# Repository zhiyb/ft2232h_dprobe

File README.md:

# ft2232h_dprobe
FT2232H debug probe

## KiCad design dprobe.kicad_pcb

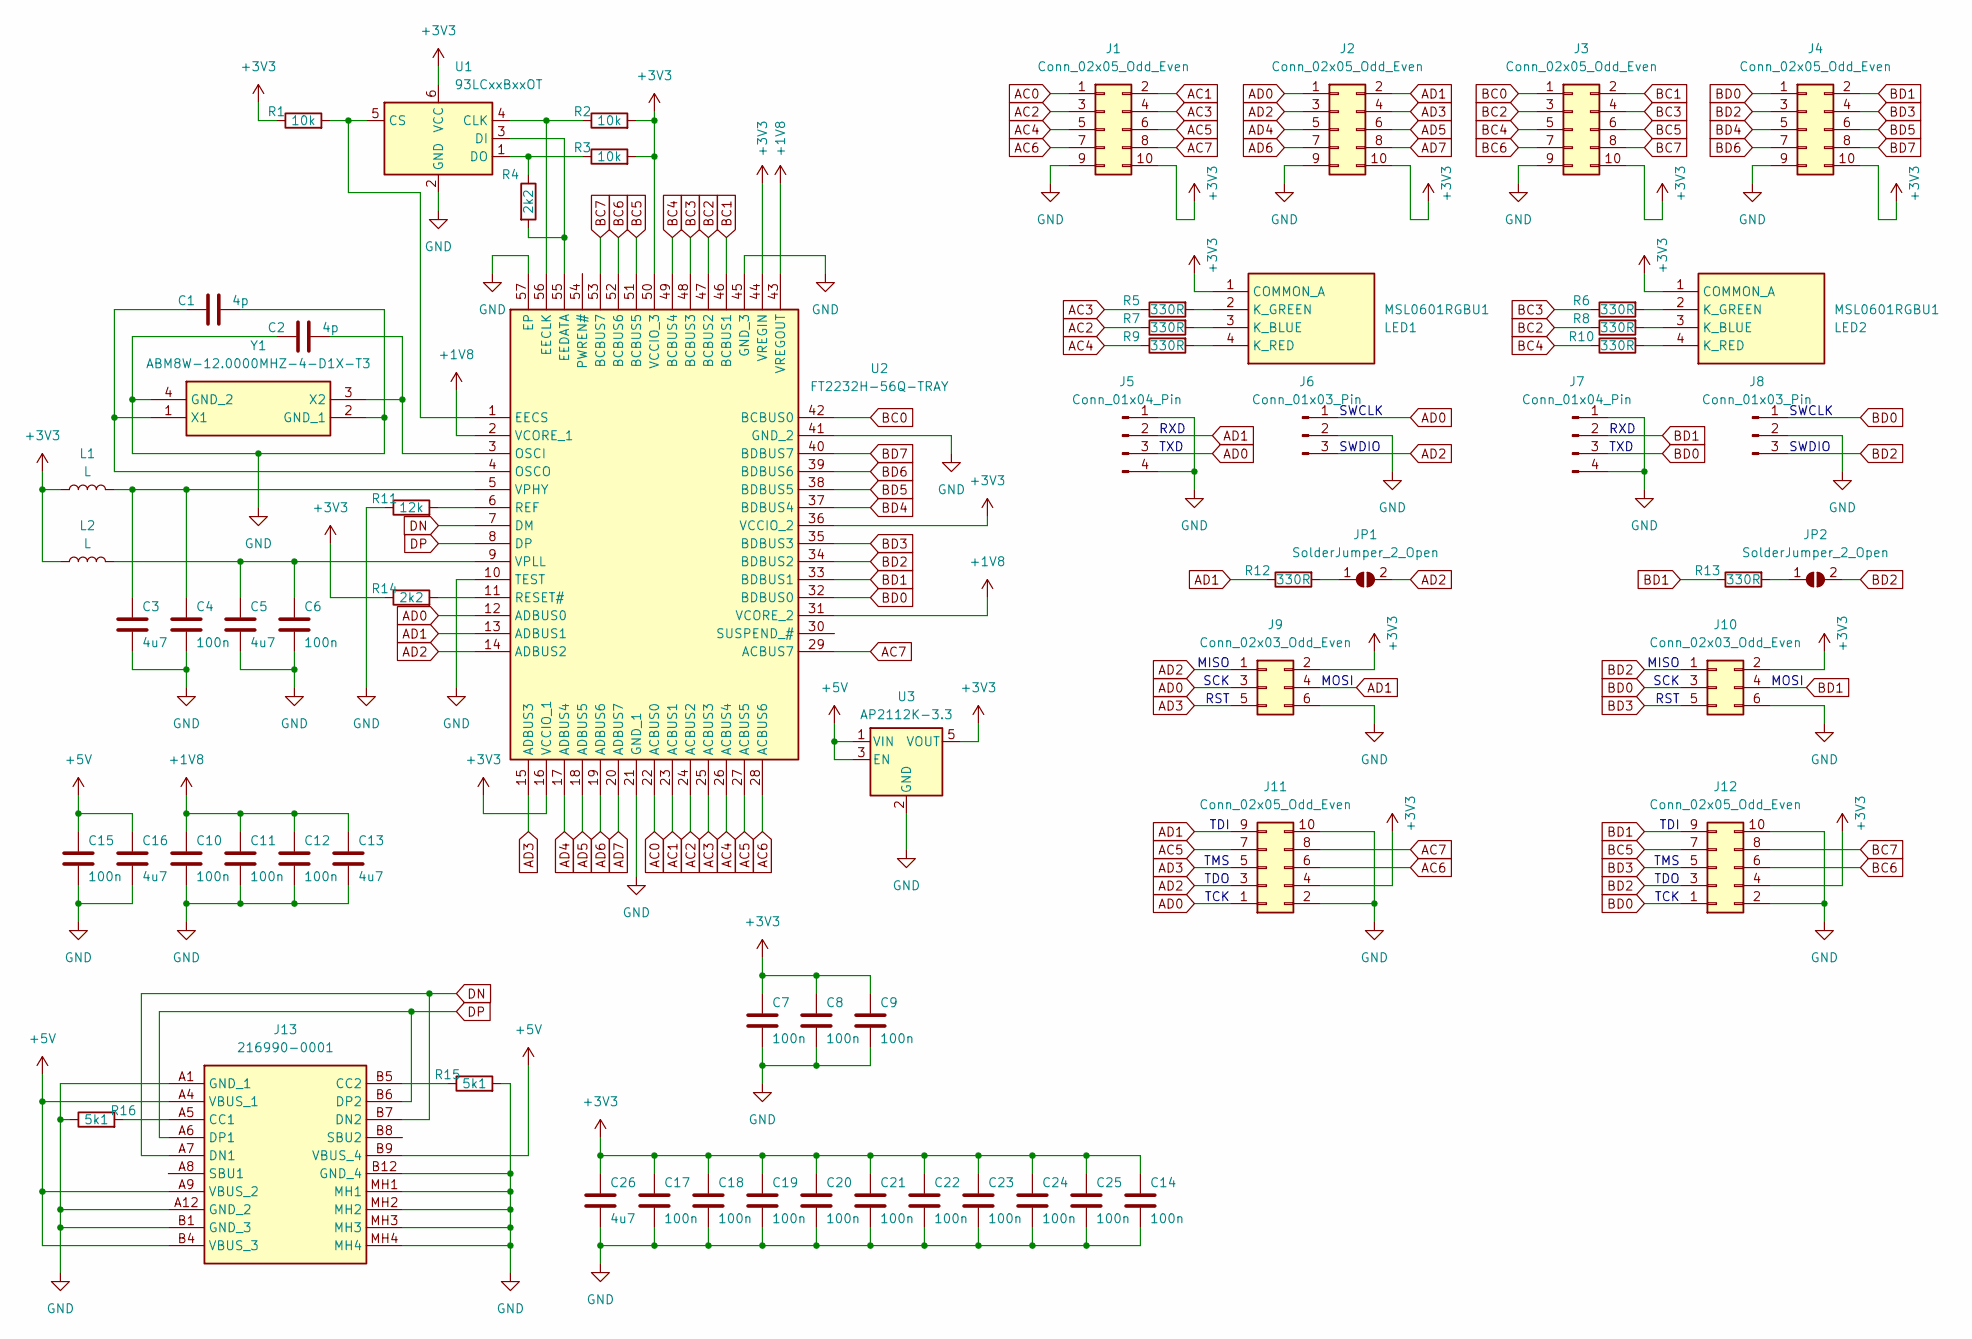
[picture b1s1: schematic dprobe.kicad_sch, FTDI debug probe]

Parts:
C1, C2: 4p; C_0402_1005Metric_Pad0.74x0.62mm_HandSolder
C3, C5, C13, C16, C26: 4u7; C_0402_1005Metric_Pad0.74x0.62mm_HandSolder
C4, C6, C7, C8, C9, C10, C11, C12, C14, C15, C17, C18, C19, C20, C21, C22, C23, C24, C25: 100n; C_0402_1005Metric_Pad0.74x0.62mm_HandSolder
J1, J2, J3, J4, J11, J12: Conn_02x05_Odd_Even; PinHeader_2x05_P2.54mm_Vertical
J5, J7: Conn_01x04_Pin; PinHeader_1x04_P2.54mm_Vertical
J6, J8: Conn_01x03_Pin; PinHeader_1x03_P2.54mm_Vertical
J9, J10: Conn_02x03_Odd_Even; PinHeader_2x03_P2.54mm_Vertical
J13: 216990-0001; 2169900001; Mouser Part Number 538-216990-0001
JP1, JP2: SolderJumper_2_Open; SolderJumper-2_P1.3mm_Open_TrianglePad1.0x1.5mm
L1, L2: L; L_0603_1608Metric_Pad1.05x0.95mm_HandSolder
LED1, LED2: MSL0601RGBU1; Mouser Part Number 755-MSL0601RGBU1
R1, R2, R3: 10k; R_0402_1005Metric_Pad0.72x0.64mm_HandSolder
R4, R14: 2k2; R_0402_1005Metric_Pad0.72x0.64mm_HandSolder
R5, R6, R7, R8, R9, R10, R12, R13: 330R; R_0402_1005Metric_Pad0.72x0.64mm_HandSolder
R11: 12k; R_0402_1005Metric_Pad0.72x0.64mm_HandSolder
R15, R16: 5k1; R_0402_1005Metric_Pad0.72x0.64mm_HandSolder
U1: 93LCxxBxxOT; SOT-23-6_Handsoldering
U2: FT2232H-56Q-TRAY; QFN50P800X800X100-57N-D; Mouser Part Number 895-FT2232H-56Q-TRAY
U3: AP2112K-3.3; SOT-23-5_HandSoldering
Y1: ABM8W-12.0000MHZ-4-D1X-T3; ABM8W480000MHZ6D1XT3; Mouser Part Number 815-8W12-4D1XT

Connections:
+1V8: C10.1, C11.1, C12.1, C13.1, U2.2 (VCORE_1), U2.31 (VCORE_2), U2.43 (VREGOUT)
+3V3: C7.1, C8.1, C9.1, C14.1, C17.1, C18.1, C19.1, C20.1, C21.1, C22.1, C23.1, C24.1, C25.1, C26.1, J1.10, J2.10, J3.10, J4.10, J9.2, J10.2, J11.4, J12.4, L1.1, L2.1, LED1.1 (COMMON_A), LED2.1 (COMMON_A), R1.1, R2.2, R3.2, R14.1, U1.6 (VCC), U2.16 (VCCIO_1), U2.36 (VCCIO_2), U2.44 (VREGIN), U2.50 (VCCIO_3), U3.5 (VOUT); also elsewhere on the board
+5V: C15.1, C16.1, J13.A4 (VBUS_1), J13.A9 (VBUS_2), J13.B4 (VBUS_3), J13.B9 (VBUS_4), U3.1 (VIN), U3.3 (EN)
AC0: J1.1, U2.22 (ACBUS0)
AC1: J1.2, U2.23 (ACBUS1)
AC2: J1.3, R7.1, U2.24 (ACBUS2)
AC3: J1.4, R5.1, U2.25 (ACBUS3)
AC4: J1.5, R9.1, U2.26 (ACBUS4)
AC5: J1.6, J11.7, U2.27 (ACBUS5); also elsewhere on the board
AC6: J1.7, J11.6, U2.28 (ACBUS6); also elsewhere on the board
AC7: J1.8, J11.8, U2.29 (ACBUS7); also elsewhere on the board
AD0: J2.1, J5.3, J6.1, J9.3, J11.1, U2.12 (ADBUS0); also elsewhere on the board
AD1: J2.2, J5.2, J9.4, J11.9, R12.1, U2.13 (ADBUS1); also elsewhere on the board
AD2: J2.3, J6.3, J9.1, J11.3, JP1.2 (B), U2.14 (ADBUS2); also elsewhere on the board
AD3: J2.4, J9.5, J11.5, U2.15 (ADBUS3); also elsewhere on the board
AD4: J2.5, U2.17 (ADBUS4)
AD5: J2.6, U2.18 (ADBUS5)
AD6: J2.7, U2.19 (ADBUS6)
AD7: J2.8, U2.20 (ADBUS7)
BC0: J3.1, U2.42 (BCBUS0)
BC1: J3.2, U2.46 (BCBUS1)
BC2: J3.3, R8.1, U2.47 (BCBUS2)
BC3: J3.4, R6.1, U2.48 (BCBUS3)
BC4: J3.5, R10.1, U2.49 (BCBUS4)
BC5: J3.6, J12.7, U2.51 (BCBUS5)
BC6: J3.7, J12.6, U2.52 (BCBUS6)
BC7: J3.8, J12.8, U2.53 (BCBUS7)
BD0: J4.1, J7.3, J8.1, J10.3, J12.1, U2.32 (BDBUS0); also elsewhere on the board
BD1: J4.2, J7.2, J10.4, J12.9, R13.1, U2.33 (BDBUS1)
BD2: J4.3, J8.3, J10.1, J12.3, JP2.2 (B), U2.34 (BDBUS2); also elsewhere on the board
BD3: J4.4, J10.5, J12.5, U2.35 (BDBUS3)
BD4: J4.5, U2.37 (BDBUS4)
BD5: J4.6, U2.38 (BDBUS5)
BD6: J4.7, U2.39 (BDBUS6)
BD7: J4.8, U2.40 (BDBUS7)
DN: J13.A7 (DN1), J13.B7 (DN2), U2.7 (DM)
DP: J13.A6 (DP1), J13.B6 (DP2), U2.8 (DP)
GND: C1.2, C2.1, C3.2, C4.2, C5.2, C6.2, C7.2, C8.2, C9.2, C10.2, C11.2, C12.2, C13.2, C14.2, C15.2, C16.2, C17.2, C18.2, C19.2, C20.2, C21.2, C22.2, C23.2, C24.2, C25.2, C26.2, J1.9, J2.9, J3.9, J4.9, J5.1, J5.4, J6.2, J7.1, J7.4, J8.2, J9.6, J10.6, J11.2, J11.10, J12.2, J12.10, J13.A1 (GND_1), J13.A12 (GND_2), J13.B1 (GND_3), J13.B12 (GND_4), J13.MH1, J13.MH2, J13.MH3, J13.MH4, R11.1, R15.2, R16.1, U1.2 (GND), U2.10 (TEST), U2.21 (GND_1), U2.41 (GND_2), U2.45 (GND_3), U2.57 (EP), U3.2 (GND), Y1.2 (GND_1), Y1.4 (GND_2); also elsewhere on the board
unnamed: J13.A5 (CC1), R16.2
unnamed: J13.B5 (CC2), R15.1
unnamed: JP1.1 (A), R12.2
unnamed: JP2.1 (A), R13.2
unnamed: LED1.3 (K_BLUE), R7.2
unnamed: LED1.2 (K_GREEN), R5.2
unnamed: LED1.4 (K_RED), R9.2
unnamed: LED2.3 (K_BLUE), R8.2
unnamed: LED2.2 (K_GREEN), R6.2
unnamed: LED2.4 (K_RED), R10.2
unnamed: R2.1, U1.4 (CLK), U2.56 (EECLK)
unnamed: R1.2, U1.5 (CS), U2.1 (EECS)
unnamed: R4.2, U1.3 (DI), U2.55 (EEDATA)
unnamed: R3.1, R4.1, U1.1 (DO)
unnamed: C2.2, U2.3 (OSCI), Y1.3 (X2)
unnamed: C1.1, U2.4 (OSCO), Y1.1 (X1)
unnamed: R11.2, U2.6 (REF)
unnamed: R14.2, U2.11 (RESET#)
unnamed: C3.1, C4.1, L1.2, U2.5 (VPHY)
unnamed: C5.1, C6.1, L2.2, U2.9 (VPLL)

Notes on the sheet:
TDO
SWCLK
RXD
TCK
RST
TXD
SCK
TDI
SWDIO
MISO
MOSI
TMS

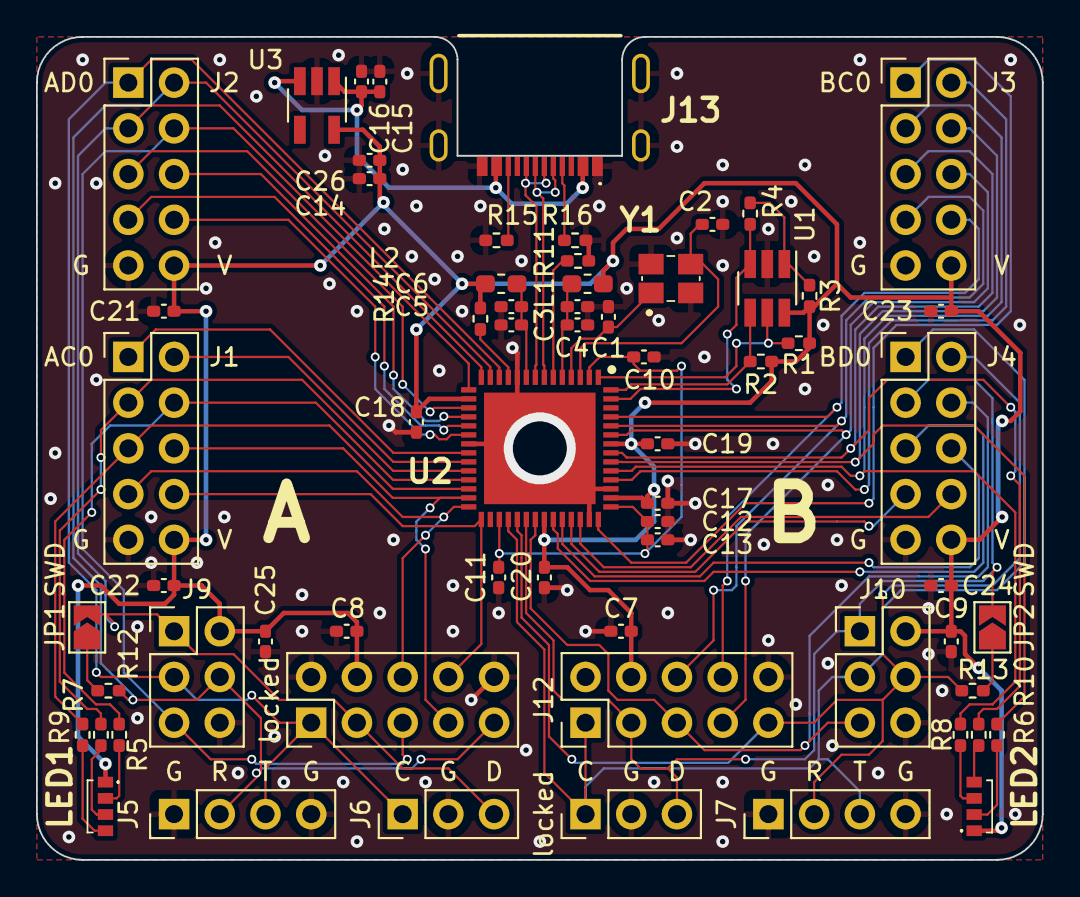
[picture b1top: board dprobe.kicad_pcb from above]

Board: 2 copper layers, 55.9 x 45.7 mm, 65 parts (0 on the bottom side), 58 nets.

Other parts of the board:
locked: Conn_02x05_Odd_Even; PinHeader_2x05_P2.54mm_Vertical
locked#2: Conn_01x03_Pin; PinHeader_1x03_P2.54mm_Vertical

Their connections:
+3V3: locked.4; also elsewhere on the board
AC5: locked.7; also elsewhere on the board
AC6: locked.6; also elsewhere on the board
AC7: locked.8; also elsewhere on the board
AD0: locked.1; also elsewhere on the board
AD1: locked.9; also elsewhere on the board
AD2: locked.3; also elsewhere on the board
AD3: locked.5; also elsewhere on the board
BD0: locked#2.1; also elsewhere on the board
BD2: locked#2.3; also elsewhere on the board
GND: locked.2, locked.10, locked#2.2; also elsewhere on the board

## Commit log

2023-07-20 Initial design
2024-01-19 Example configs for avrdude and openocd
2024-02-24 FT_PROG device template
